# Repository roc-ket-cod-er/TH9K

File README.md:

## TH9K
A 9-key Macro pad with 6 LEDs, an OLED and a rotary encoder designed to go under the space bar so your thumbs too can feel useful.

## BOM
- 9x KeyBoard switch
- 9x Diodes
- 6x RGB LED
- Some kind of screws, probably M3
- 1x 0.91" 128x32 OLED Display
- 1x EC11 Rotary Encoder
- 1x XIAO RP2040
- 1x Case

In other words, I have used 9 keyboard switches, a rotary encoder, and an OLED. The OLED goes under the big rectangualar hole, the rotary encoder in the left squarish one, the leds will be visible throught the right square hole, and the main switches and stuff in the last hole as shown below:

## Schematic
I used the following schematic:

## PCB
Which I routed into the following pcb:

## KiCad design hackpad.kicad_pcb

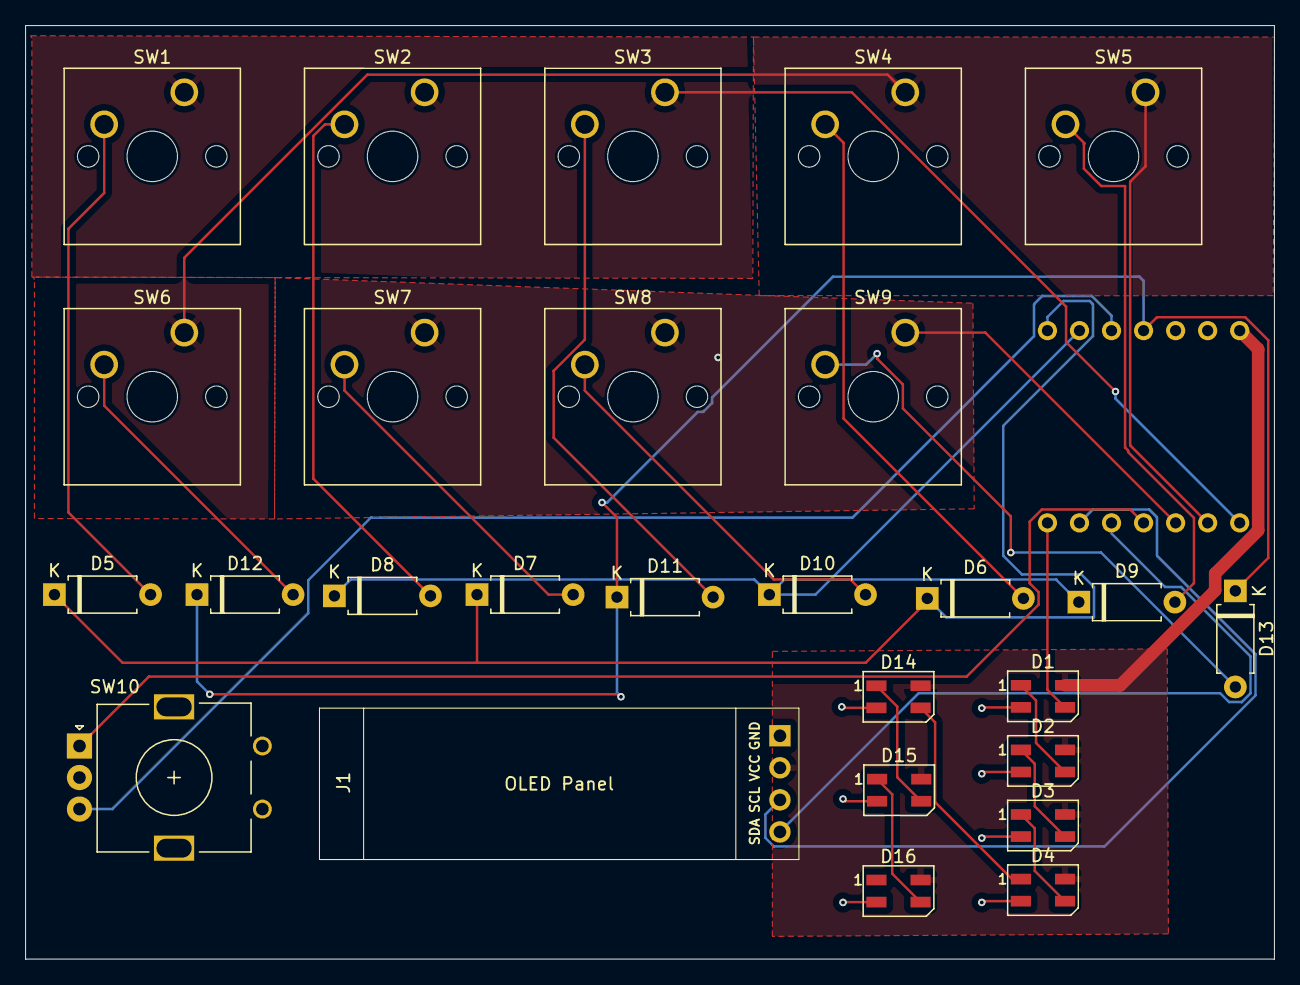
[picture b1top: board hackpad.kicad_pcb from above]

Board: 2 copper layers, 99.0 x 74.0 mm, 28 parts (1 on the bottom side), 28 nets.

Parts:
D1, D2, D3, D4, D14, D15, D16: SK6812MINI; LED_SK6812MINI_PLCC4_3.5x3.5mm_P1.75mm
D5, D6, D7, D8, D9, D10, D11, D12, D13: D_45deg; D_A-405_P7.62mm_Horizontal
J1: Conn_01x04_Pin; SSD1306-0.91-OLED-4pin-128x32
SW1, SW2, SW3, SW4, SW5, SW6, SW7, SW8, SW9: SW_Push; SW_Cherry_MX_1.00u_PCB
SW10: RotaryEncoder_Switch; RotaryEncoder_Alps_EC11E_Vertical_H20mm
U1: XIAO-RP2040-DIP

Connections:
+5V: D1.4 (VDD), D2.4 (VDD), D3.4 (VDD), D4.4 (VDD), D14.4 (VDD), D15.4 (VDD), D16.4 (VDD), J1.2, U1.14 (VBUS)
A: SW10.A, U1.4 (GPIO29/ADC3/A3)
B: SW10.B, U1.10 (GPIO4/MISO)
C1: SW1.1, SW2.1, SW3.1, U1.1 (GPIO26/ADC0/A0)
C2: SW4.1, SW5.1, SW6.1, U1.2 (GPIO27/ADC1/A1)
C3: SW7.1, SW8.1, SW9.1, U1.3 (GPIO28/ADC2/A2)
GND: D1.2 (VSS), D2.2 (VSS), D3.2 (VSS), D4.2 (VSS), D14.2 (VSS), D15.2 (VSS), D16.2 (VSS), J1.1, SW10.C, U1.13 (GND)
unnamed: D1.3 (DIN), U1.7 (GPIO0/TX)
unnamed: D1.1 (DOUT), D2.3 (DIN)
unnamed: D2.1 (DOUT), D3.3 (DIN)
unnamed: D3.1 (DOUT), D4.3 (DIN)
unnamed: D5.2 (A), SW1.2
unnamed: D6.2 (A), SW4.2
unnamed: D7.2 (A), SW7.2
unnamed: D8.2 (A), SW2.2
unnamed: D9.2 (A), SW5.2
unnamed: D10.2 (A), SW8.2
unnamed: D11.2 (A), SW3.2
unnamed: D12.2 (A), SW6.2
unnamed: D13.2 (A), SW9.2
unnamed: D4.1 (DOUT), D14.3 (DIN)
unnamed: D14.1 (DOUT), D15.3 (DIN)
unnamed: D15.1 (DOUT), D16.3 (DIN)
unnamed: J1.3, U1.6 (GPIO7/SCL)
unnamed: J1.4, U1.5 (GPIO6/SDA)
R1: D5.1 (K), D6.1 (K), D7.1 (K), U1.8 (GPIO1/RX)
R2: D8.1 (K), D9.1 (K), D10.1 (K), U1.9 (GPIO2/SCK)
R3: D11.1 (K), D12.1 (K), D13.1 (K), U1.11 (GPIO3/MOSI)

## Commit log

2025-05-27 Rename Untitled v10.step to CAD/Untitled v10.step
2025-05-27 Added the pcb
2025-05-27 Rename hackpad.kicad_pcb to PCB/hackpad.kicad_pcb
2025-05-27 added gerbers
2025-05-27 Updated STEP
2025-05-27 Rename hackpad.kicad_pro to PCB/hackpad.kicad_pro
2025-05-27 Rename hackpad.kicad_sch to PCB/hackpad.kicad_sch
2025-05-27 Added case files
2025-05-30 Rename main.py to main.py
